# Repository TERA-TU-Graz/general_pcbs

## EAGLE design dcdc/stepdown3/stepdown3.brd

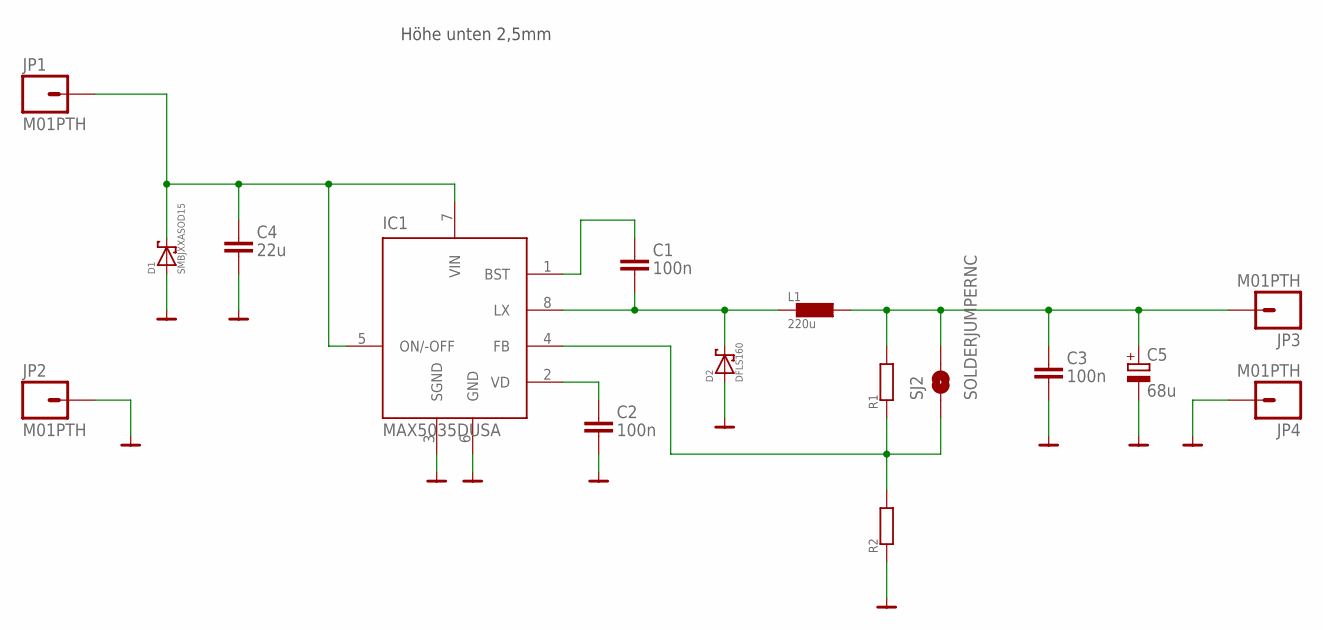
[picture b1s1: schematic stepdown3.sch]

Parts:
C1, C2, C3: 100n; C0805
C4: 22u; CKG57N
C5: 68u; CT6032
D1: SMBJXXASOD15; SOD15
D2: DFLS160; POWERDI123
IC1: MAX5035DUSA; SO08
JP1, JP2, JP3, JP4: M01PTH; 1X01
L1: 220u; L_RM5MM
R1, R2: R; R0805
SJ2: SOLDERJUMPERNC; SJ_2S

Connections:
GND: C2.1, C3.1, C4.P$1 (1), C5.-, D1.A, D2.A, IC1.3 (SGND), IC1.6 (GND), JP2.1, JP4.1, R2.1
LX: C1.1, D2.K (D), IC1.8 (LX), L1.P$1 (1)
unnamed: IC1.4 (FB), R1.1, R2.2, SJ2.1
unnamed: C1.2, IC1.1 (BST)
unnamed: C2.2, IC1.2 (VD)
VIN: C4.P$2 (2), D1.K, IC1.5 (ON/-OFF), IC1.7 (VIN), JP1.1
VOUT: C3.2, C5.+, JP3.1, L1.P$2 (2), R1.2, SJ2.2

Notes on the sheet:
Höhe unten 2,5mm

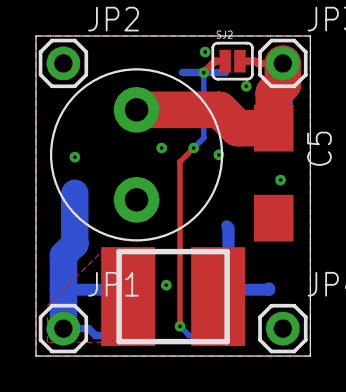
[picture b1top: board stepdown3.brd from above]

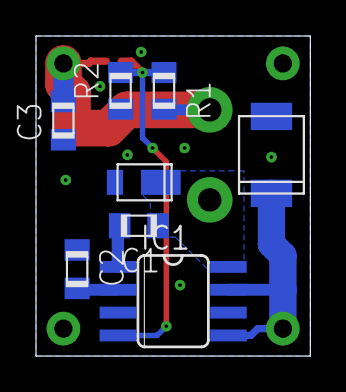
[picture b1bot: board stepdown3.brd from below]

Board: 4 copper layers, 15.2 x 17.8 mm, 16 parts (8 on the bottom side), 7 nets.

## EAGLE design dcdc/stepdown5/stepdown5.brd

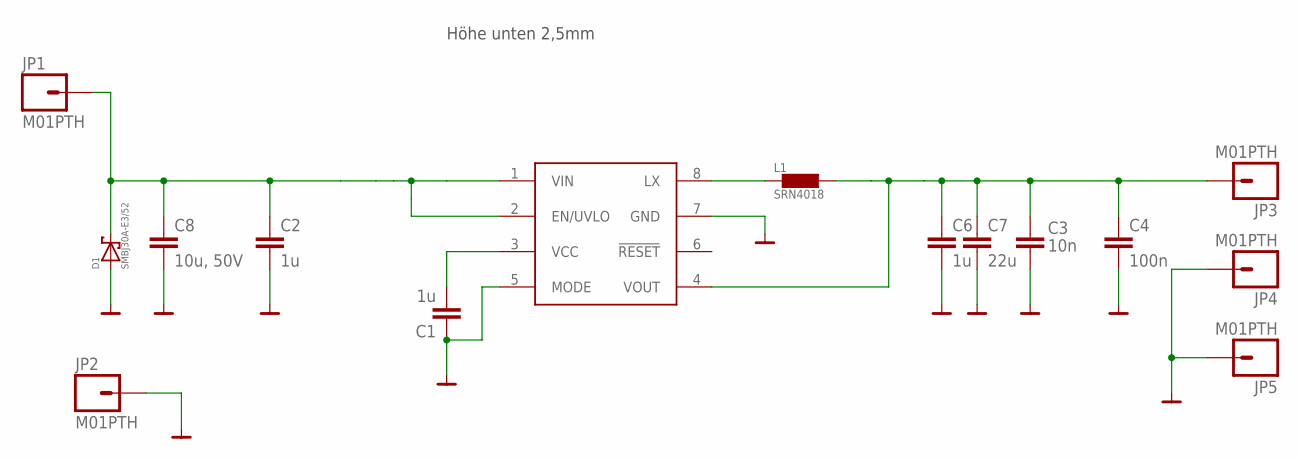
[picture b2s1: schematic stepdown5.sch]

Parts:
C1: 1u; C0603
C2: 1u; C1206
C3: 10n; C0805
C4: 100n; C0805
C6: 1u; C0805
C7: 22u; C1206
C8: 10u, 50V; C1210
D1: SMBJ30A-E3/52; SOD15
IC1: MAX15062; 8TDFN
JP1, JP2, JP3, JP4, JP5: M01PTH; 1X01
L1: SRN4018

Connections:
GND: C1.1, C2.2, C3.1, C4.2, C6.2, C7.2, C8.2, D1.A, IC1.5 (MODE), IC1.7 (GND), JP2.1, JP4.1, JP5.1
unnamed: IC1.8 (LX), L1.P$1 (1)
unnamed: C1.2, IC1.3 (VCC)
VIN: C2.1, C8.1, D1.K, IC1.1 (VIN), IC1.2 (EN/UVLO), JP1.1
VOUT: C3.2, C4.1, C6.1, C7.1, IC1.4 (VOUT), JP3.1, L1.P$2 (2)

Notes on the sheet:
Höhe unten 2,5mm

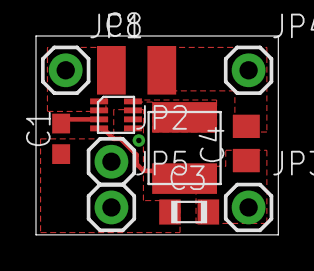
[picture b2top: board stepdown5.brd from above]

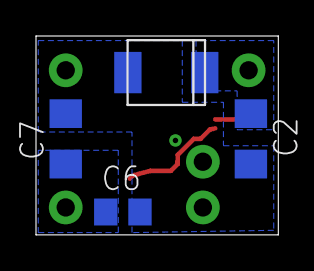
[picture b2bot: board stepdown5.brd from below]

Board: 4 copper layers, 13.5 x 11.0 mm, 15 parts (4 on the bottom side), 5 nets.

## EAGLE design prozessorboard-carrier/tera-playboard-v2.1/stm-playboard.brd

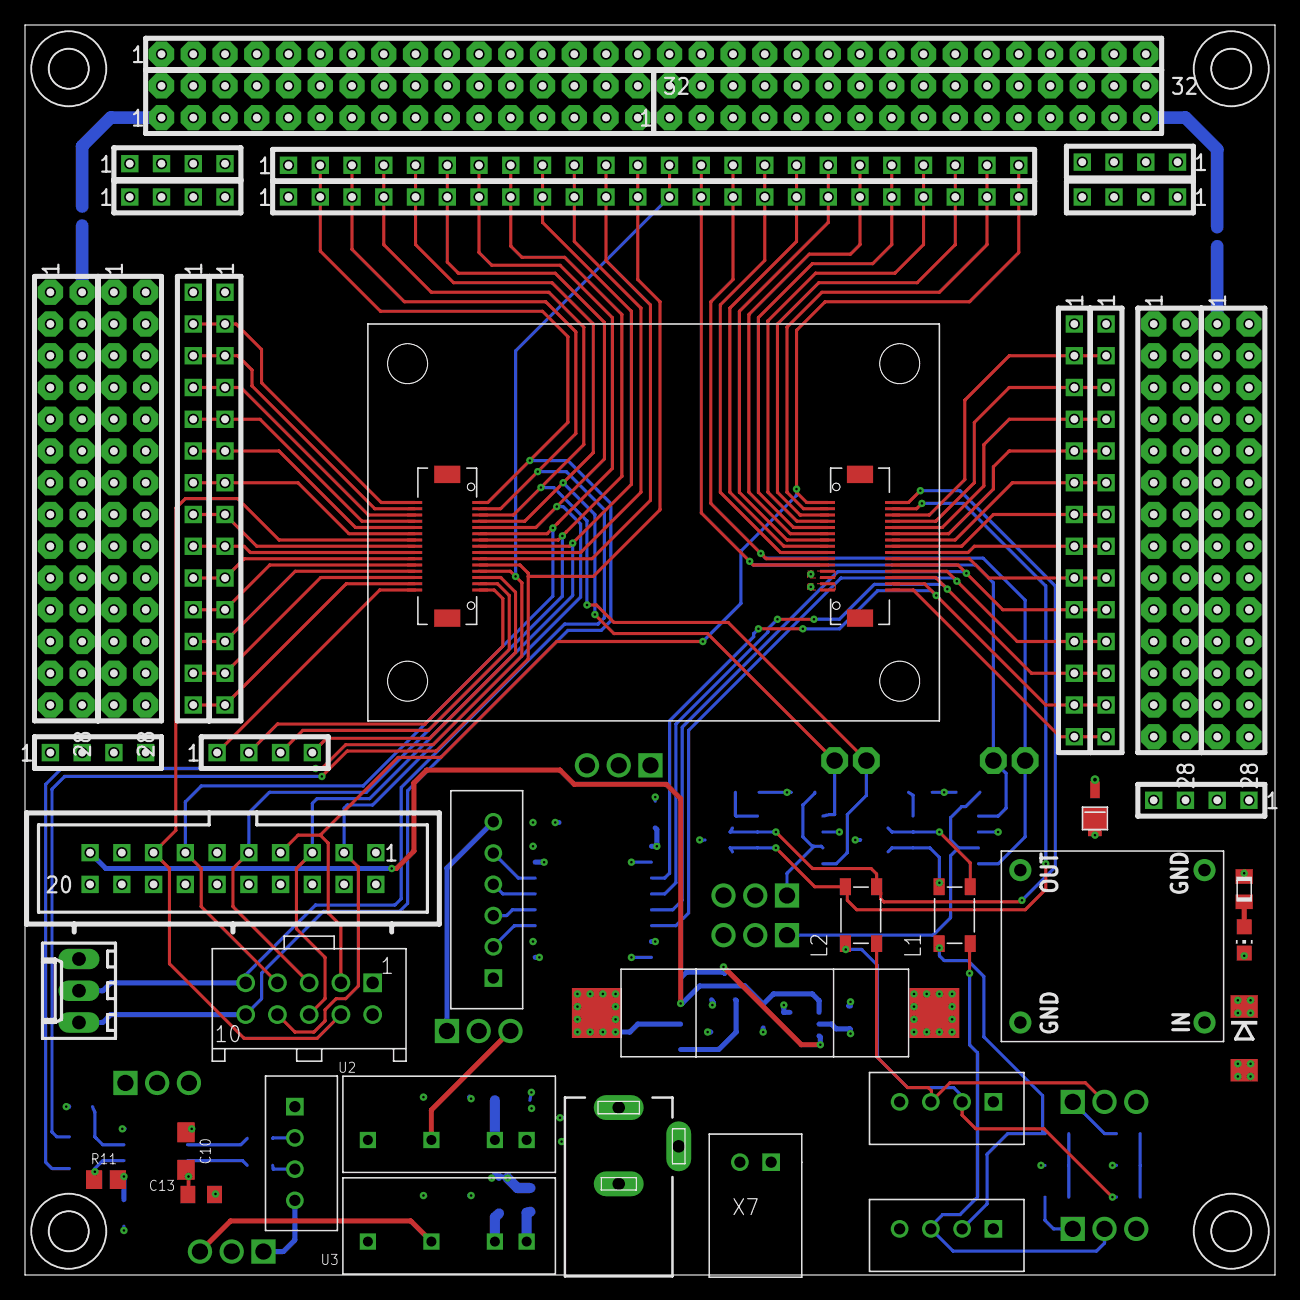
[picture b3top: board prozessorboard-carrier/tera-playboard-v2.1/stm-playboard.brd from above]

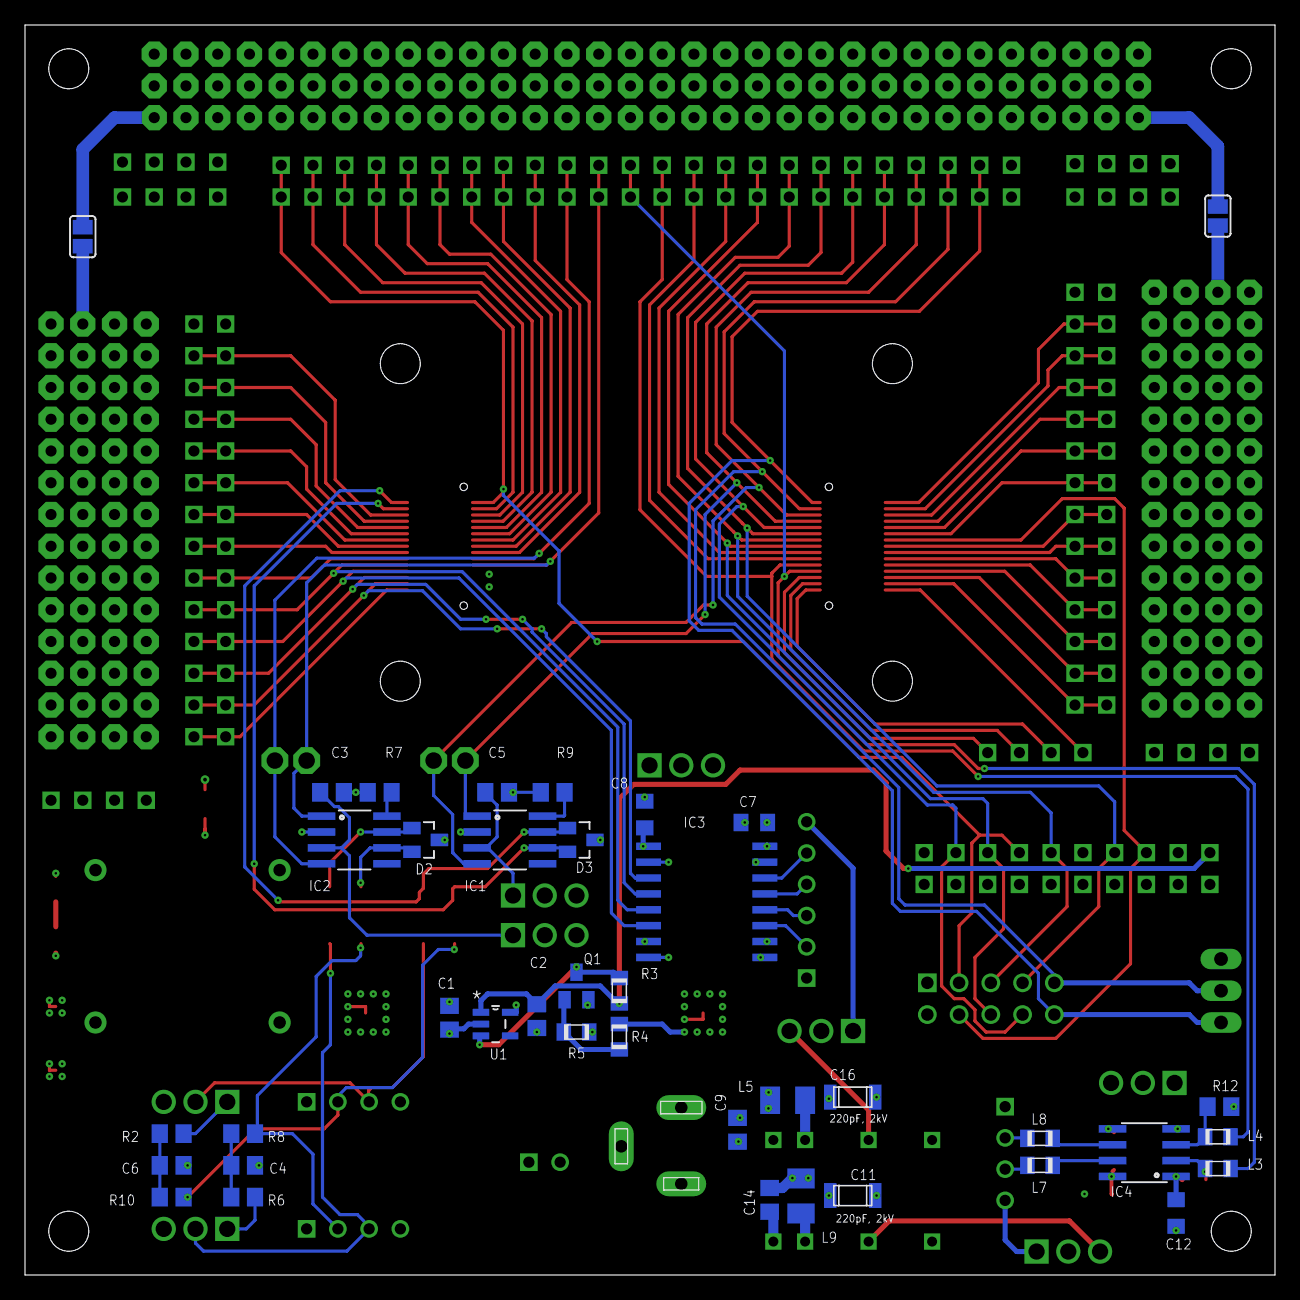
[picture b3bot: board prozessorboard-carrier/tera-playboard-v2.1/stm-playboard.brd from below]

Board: 4 copper layers, 100.0 x 100.0 mm, 98 parts (39 on the bottom side), 104 nets.

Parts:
C1, C2: 1u; C0805
C3, C5, C7, C8, C12, C13: 100n; C0805
C4, C6: 47n; C0805
C9, C14: 4,7uF, 50V; C0805
C10: 10u; SMC_A
C11, C16: 220pF, 2kV; C1210_HV
D1: 18V; DO214AA
D2, D3: NUP2105LT1G|SOT23; SOT23
H1, H2, H3, H4: MOUNT-HOLE3.2; 3,2
IC1, IC2: SN65HVD230D; SO08
IC3: ISO7241; R-PDSO-G16
IC4: ADUM1250; SO08
J1: DCJ0303
JTAG: X20R-IDC
L1, L2: ACT45B-510-2P-TL003; ACT45B
L3, L4, L7, L8: R0805
L5, L9: 4,7uH, 1,2A; L3225M
LED1: green; CHIP-LED0805
PROZ1: STM32F4_PROZESSORBOARDRPZ; STM32F4_PROZESSORBOARD
Q1: BSH105; SOT23
R1: 240R; R0805
R2, R6, R8, R10: 60R; R0805
R3, R4: 10k; R0805
R5: 15k; R0805
R7, R9: 50k; R0805
R11, R12: 15K; R0805
SERIAL: RS232V; 6410-03
SJ1, SJ2: SJ
S_CAN1, S_CAN1_ROFF, S_CAN2, S_CAN2_ROFF: JUMPER_OR; J_OR
S_I2C, S_I2C1: JUMPER_OR; J_OR
S_SPI, S_SPI1: JUMPER_OR; J_OR
TERA-DC/DC1: MAX5035_STEPDOWN3
TERA-DEBUG: TERA-PROG-DEBUG-10GERADE; 90130-1110
TP1, TP2, TP3, TP4: TPPAD1-13; P1-13
U1: ADP122AUJZ-3.3-R7; SOT95P280X100-5N
U2, U3: TMR 1-1211; TMR_1-??1?
U$2: FUSE20X5SMD; FUSE20X5-SMD
U$3: SM2T3V3A
X1, X23: X24R-SIL
X2, X14, X16, X20: X14R-SIL
X3, X4, X5, X6, X17, X18, X19: X04R-SIL
X7: S2B-XH
X8, X22: X32N-DIL
X9, X21, X24: B4B-XH
X10, X11, X12, X13: X28N-DIL
X15: X32N-SIL
X26: B6B-XH

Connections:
+3V3: C1.1, JTAG.1, PROZ1.45, PROZ1.46, R1.2, S_CAN1.P$1, S_CAN2.P$1, S_I2C.P$1, S_SPI.P$1, TERA-DC/DC1.VOUT, TERA-DEBUG.2, U1.5, U$3.P$2, X3.3, X3.4, X4.3, X4.4, X5.3, X5.4, X6.3, X6.4, X17.3, X17.4, X18.3, X18.4
+5V: C2.1, JTAG.19, R3.2, U1.1
CAN1_H: L2.P$1, S_CAN1_ROFF.P$1, X9.P$3
CAN1_L: L2.P$3, R10.2, X9.P$2
CAN2_H: L1.P$1, S_CAN2_ROFF.P$1, X21.P$3
CAN2_H0: D2.1, IC2.7, L1.P$2
CAN2_L: L1.P$3, R8.2, X21.P$2
CAN2_L0: D2.2, IC2.6, L1.P$4
CANP_H: D3.1, IC1.7, L2.P$2, PROZ1.31
CANP_L: D3.2, IC1.6, L2.P$4, PROZ1.32
GND: C1.2, C2.2, C3.2, C4.2, C5.2, C6.2, C8.1, C9.2, C11.P$1, C12.1, C14.2, C16.P$1, D1.A, D2.3, D3.3, IC1.2, IC2.2, IC3.2, IC3.8, IC4.4, J1.3, JTAG.4, JTAG.6, JTAG.8, JTAG.10, JTAG.12, JTAG.14, JTAG.16, JTAG.18, JTAG.20, LED1.C, PROZ1.47, PROZ1.48, Q1.2, R5.1, R7.1, R9.1, SERIAL.1, TERA-DC/DC1.GND@1, TERA-DC/DC1.GND@2, TERA-DEBUG.1, U1.2, U2.P$1, U3.P$1, U$3.P$1, U$3.P$11, X1.1, X2.1, X3.1, X3.2, X4.1, X4.2, X5.1, X5.2, X6.1, X6.2, X7.P$1, X9.P$1, X14.1, X16.1, X17.1, X17.2, X18.1, X18.2, X20.1, X21.P$1, X23.1
GND_SLAVE: C10.-, C11.P$2, C13.1, IC4.5, U3.P$6, X24.P$1
I2C1-SCL: IC4.3, L4.2, R12.1
I2C1-SCL1: L8.1, X24.P$2
I2C1-SDA: IC4.2, L3.2, R11.1
I2C1-SDA1: L7.1, X24.P$3
LDO_EN: Q1.3, R3.1, U1.3
unnamed: LED1.A, R1.1
unnamed: C6.1, R2.1, R10.1
unnamed: PROZ1.6, X19.4
unnamed: SJ2.1, X8.31
unnamed: SJ1.2, X12.2
unnamed: PROZ1.1, X19.1
unnamed: PROZ1.4, X19.3
unnamed: PROZ1.2, X19.2
unnamed: SJ2.2, X13.1
unnamed: SJ1.1, X22.1
unnamed: Q1.1, R4.1, R5.2
unnamed: IC4.7, L7.2
unnamed: IC4.6, L8.2
unnamed: C5.1, IC1.3, S_CAN1.P$2
unnamed: C3.1, IC2.3, S_CAN2.P$2
unnamed: IC1.8, R9.2
unnamed: C4.1, R6.1, R8.1
unnamed: R2.2, S_CAN1_ROFF.P$2
unnamed: IC2.8, R7.2
unnamed: R6.2, S_CAN2_ROFF.P$2
unnamed: C12.2, IC4.1, R11.2, R12.2, S_I2C.P$2
unnamed: C8.2, IC3.1, IC3.7, S_SPI.P$2
unnamed: L5.1, U2.P$2
unnamed: S_I2C1.P$2, X24.P$4
unnamed: S_I2C1.P$3, U3.P$4
unnamed: S_SPI1.P$2, X26.P$6
unnamed: S_SPI1.P$3, U2.P$4
unnamed: L9.1, U3.P$2
NRST: JTAG.15, PROZ1.17, TERA-DEBUG.4
PA0: PROZ1.7, X2.12, X16.12
PA1: PROZ1.5, X2.13, X16.13
PA2: PROZ1.3, X2.14, X16.14
PA3: PROZ1.44, X14.14, X20.14
PA4: IC3.3, PROZ1.43, X14.13, X20.13
PA5: IC3.4, PROZ1.60, X14.12, X20.12
PA6: IC3.6, PROZ1.42, X14.11, X20.11
PA7: IC3.5, PROZ1.41, X14.10, X20.10
PA8: PROZ1.56, X1.21, X23.21
PA9: PROZ1.57, X1.22, X23.22
PA10: PROZ1.58, X1.23, X23.23
PA11: IC1.4, PROZ1.26, TP2.TP, X1.4, X23.4
PA12: IC1.1, PROZ1.24, TP1.TP, X1.5, X23.5
PA13: JTAG.7, PROZ1.59, TERA-DEBUG.3, X1.24, X23.24
PA14: JTAG.9, PROZ1.18, TERA-DEBUG.5, X1.8, X23.8
PA15: JTAG.5, PROZ1.16, TERA-DEBUG.6, X1.9, X23.9
PB0: PROZ1.38, X14.7, X20.7
PB1: PROZ1.37, X14.6, X20.6
PB2: PROZ1.36, X14.5, X20.5
PB3: JTAG.13, PROZ1.20, TERA-DEBUG.7, X1.7, X23.7
PB4: JTAG.3, PROZ1.22, TERA-DEBUG.8, X1.6, X23.6
PB5: PROZ1.25, X2.4, X16.4
PB6: PROZ1.14, X1.10, X23.10
PB7: PROZ1.12, X1.11, X23.11
PB8: L4.1, PROZ1.10, X1.12, X23.12
PB9: L3.1, PROZ1.8, X1.13, X23.13
PB10: PROZ1.35, X14.4, X20.4
PB11: PROZ1.34, X14.3, X20.3
PB12: IC2.4, PROZ1.50, TP4.TP, X1.15, X23.15
PB13: IC2.1, PROZ1.49, TP3.TP, X1.14, X23.14
PB14: PROZ1.33, X14.2, X20.2
PB15: PROZ1.51, X1.16, X23.16
PC0: PROZ1.15, X2.8, X16.8
PC1: PROZ1.13, X2.9, X16.9
PC2: PROZ1.11, X2.10, X16.10
PC3: PROZ1.9, X2.11, X16.11
PC4: PROZ1.40, X14.9, X20.9
PC5: PROZ1.39, X14.8, X20.8
PC6: PROZ1.52, X1.17, X23.17
PC7: PROZ1.53, X1.18, X23.18
PC8: PROZ1.54, X1.19, X23.19
PC9: PROZ1.55, X1.20, X23.20
PC10: PROZ1.28, SERIAL.2, TERA-DEBUG.9, X1.3, X23.3
PC11: PROZ1.30, SERIAL.3, TERA-DEBUG.10, X1.2, X23.2
PC12: PROZ1.29, X2.2, X16.2
PC13: PROZ1.23, X2.5, X16.5
PC14: PROZ1.21, X2.6, X16.6
PC15: PROZ1.19, X2.7, X16.7
PD2: PROZ1.27, X2.3, X16.3
SPI_MISO: IC3.11, X26.P$2
SPI_MOSI: IC3.12, X26.P$3
SPI_NCS: IC3.14, X26.P$5
SPI_SCK: IC3.13, X26.P$4
SPI_V+: C7.2, IC3.10, IC3.16, S_SPI1.P$1
SPI_V-: C7.1, C16.P$2, IC3.9, IC3.15, U2.P$6, X26.P$1
VBAT: J1.1, R4.2, U$2.P$3, X7.P$2
VBAT_FUSED: C9.1, C14.1, D1.C, L5.2, L9.2, TERA-DC/DC1.VIN, U$2.P$4, X9.P$4, X21.P$4
VDD-ISO1: C10.+, C13.2, IC4.8, S_I2C1.P$1

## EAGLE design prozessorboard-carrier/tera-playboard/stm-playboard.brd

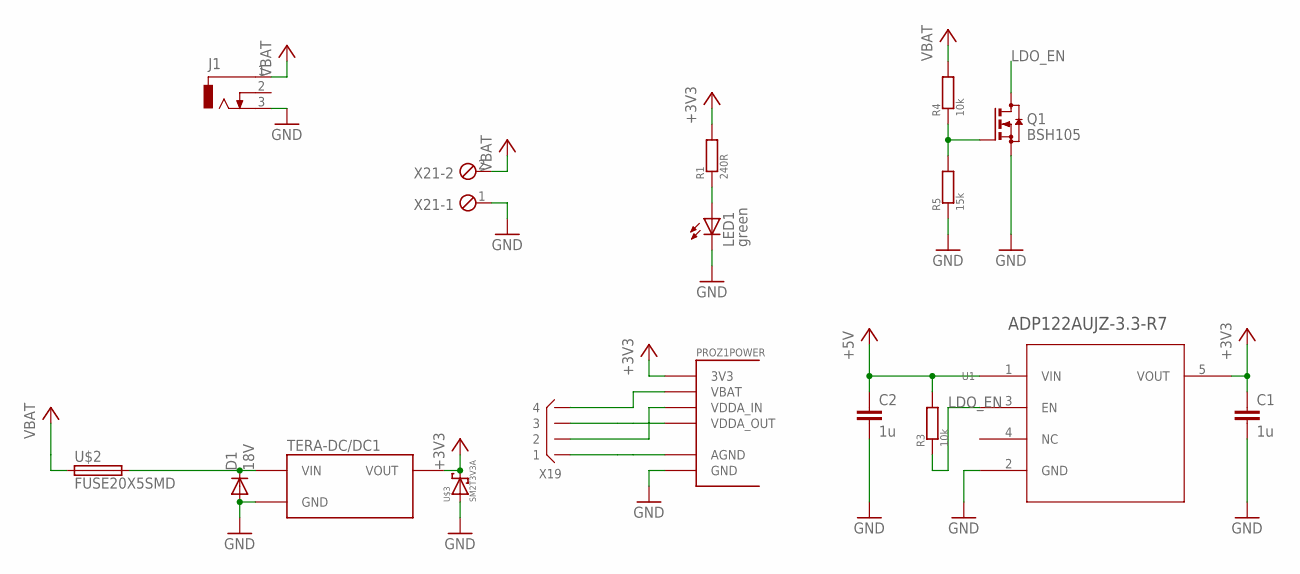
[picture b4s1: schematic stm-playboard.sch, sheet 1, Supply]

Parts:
C1, C2: 1u; C0805
D1: 18V; DO214AA
J1: DCJ0303
LED1: green; CHIP-LED0805
PROZ1: STM32F4_PROZESSORBOARDRPZ; STM32F4_PROZESSORBOARD
Q1: BSH105; SOT23
R1: 240R; R0805
R3, R4: 10k; R0805
R5: 15k; R0805
TERA-DC/DC1: MAX5035_STEPDOWN3
U1: ADP122AUJZ-3.3-R7; SOT95P280X100-5N
U$2: FUSE20X5SMD; FUSE20X5-SMD
U$3: SM2T3V3A
X19: X04N; X04N-SIL
X21: MPT2; 2POL254

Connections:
+3V3: C1.1, PROZ1.45 (3V3), PROZ1.46 (3V3), R1.2, TERA-DC/DC1.VOUT, U1.5 (VOUT), U$3.P$2; also elsewhere on the board
+5V: C2.1, R3.2, U1.1 (VIN); also elsewhere on the board
GND: C1.2, C2.2, D1.A, J1.3, LED1.C, PROZ1.47 (GND), PROZ1.48 (GND), Q1.2 (S), R5.1, TERA-DC/DC1.GND@1 (GND), TERA-DC/DC1.GND@2 (GND), U1.2 (GND), U$3.P$1, U$3.P$11, X21.1; also elsewhere on the board
LDO_EN: Q1.3 (D), R3.1, U1.3 (EN)
unnamed: D1.C, TERA-DC/DC1.VIN, U$2.P$4 (2)
unnamed: LED1.A, R1.1
unnamed: PROZ1.6 (VBAT), X19.4
unnamed: PROZ1.1 (AGND), X19.1
unnamed: PROZ1.4 (VDDA_OUT), X19.3
unnamed: PROZ1.2 (VDDA_IN), X19.2
unnamed: Q1.1 (G), R4.1, R5.2
VBAT: J1.1, R4.2, U$2.P$3 (1), X21.2; also elsewhere on the board

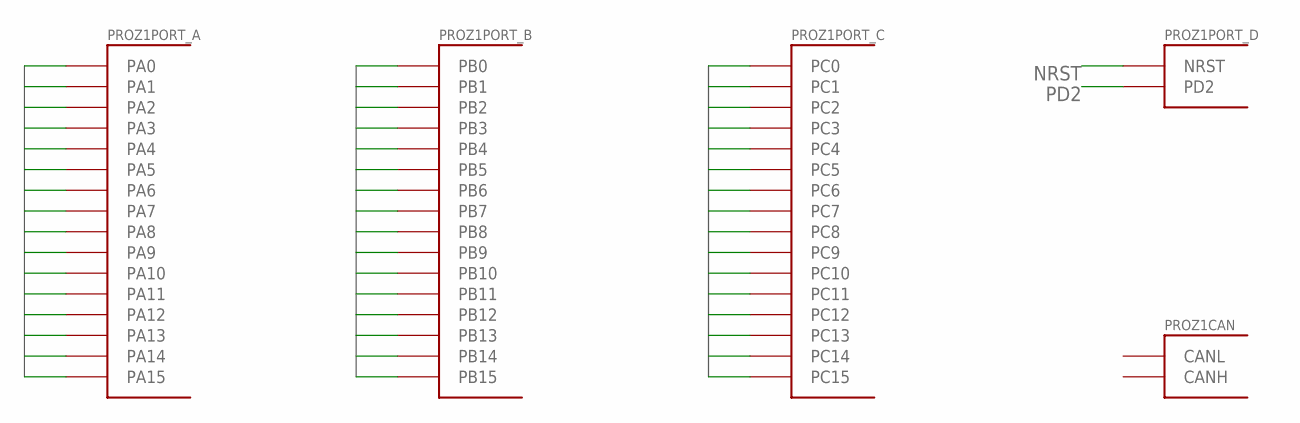
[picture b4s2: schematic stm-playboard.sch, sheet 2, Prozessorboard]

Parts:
PROZ1: STM32F4_PROZESSORBOARDRPZ; STM32F4_PROZESSORBOARD

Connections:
NRST: PROZ1.17 (NRST); also elsewhere on the board
PA0: PROZ1.7 (PA0); also elsewhere on the board
PA1: PROZ1.5 (PA1); also elsewhere on the board
PA2: PROZ1.3 (PA2); also elsewhere on the board
PA3: PROZ1.44 (PA3); also elsewhere on the board
PA4: PROZ1.43 (PA4); also elsewhere on the board
PA5: PROZ1.60 (PA5); also elsewhere on the board
PA6: PROZ1.42 (PA6); also elsewhere on the board
PA7: PROZ1.41 (PA7); also elsewhere on the board
PA8: PROZ1.56 (PA8); also elsewhere on the board
PA9: PROZ1.57 (PA9); also elsewhere on the board
PA10: PROZ1.58 (PA10); also elsewhere on the board
PA11: PROZ1.26 (PA11); also elsewhere on the board
PA12: PROZ1.24 (PA12); also elsewhere on the board
PA13: PROZ1.59 (PA13); also elsewhere on the board
PA14: PROZ1.18 (PA14); also elsewhere on the board
PA15: PROZ1.16 (PA15); also elsewhere on the board
PB0: PROZ1.38 (PB0); also elsewhere on the board
PB1: PROZ1.37 (PB1); also elsewhere on the board
PB2: PROZ1.36 (PB2); also elsewhere on the board
PB3: PROZ1.20 (PB3); also elsewhere on the board
PB4: PROZ1.22 (PB4); also elsewhere on the board
PB5: PROZ1.25 (PB5); also elsewhere on the board
PB6: PROZ1.14 (PB6); also elsewhere on the board
PB7: PROZ1.12 (PB7); also elsewhere on the board
PB8: PROZ1.10 (PB8); also elsewhere on the board
PB9: PROZ1.8 (PB9); also elsewhere on the board
PB10: PROZ1.35 (PB10); also elsewhere on the board
PB11: PROZ1.34 (PB11); also elsewhere on the board
PB12: PROZ1.50 (PB12); also elsewhere on the board
PB13: PROZ1.49 (PB13); also elsewhere on the board
PB14: PROZ1.33 (PB14); also elsewhere on the board
PB15: PROZ1.51 (PB15); also elsewhere on the board
PC0: PROZ1.15 (PC0); also elsewhere on the board
PC1: PROZ1.13 (PC1); also elsewhere on the board
PC2: PROZ1.11 (PC2); also elsewhere on the board
PC3: PROZ1.9 (PC3); also elsewhere on the board
PC4: PROZ1.40 (PC4); also elsewhere on the board
PC5: PROZ1.39 (PC5); also elsewhere on the board
PC6: PROZ1.52 (PC6); also elsewhere on the board
PC7: PROZ1.53 (PC7); also elsewhere on the board
PC8: PROZ1.54 (PC8); also elsewhere on the board
PC9: PROZ1.55 (PC9); also elsewhere on the board
PC10: PROZ1.28 (PC10); also elsewhere on the board
PC11: PROZ1.30 (PC11); also elsewhere on the board
PC12: PROZ1.29 (PC12); also elsewhere on the board
PC13: PROZ1.23 (PC13); also elsewhere on the board
PC14: PROZ1.21 (PC14); also elsewhere on the board
PC15: PROZ1.19 (PC15); also elsewhere on the board
PD2: PROZ1.27 (PD2); also elsewhere on the board

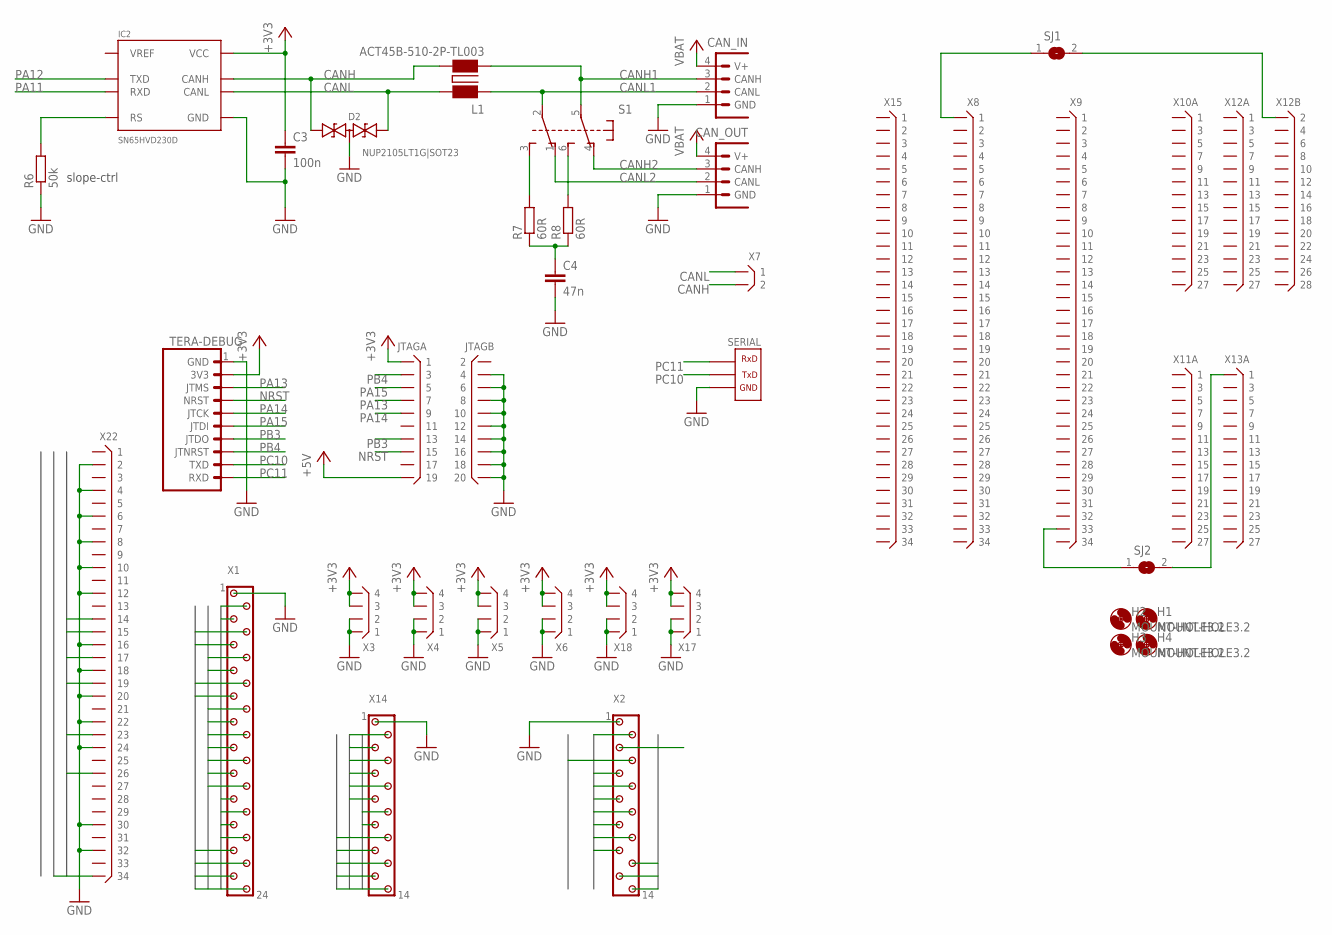
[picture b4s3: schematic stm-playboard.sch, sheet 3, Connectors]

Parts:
C3: 100n; C0805
C4: 47n; C0805
CAN_IN: CIOC_4-1-FV-A_CAN-BELEGUNG; CIOC_4-1-FV
CAN_OUT: CIOC_4-1-FV-A_CAN-BELEGUNG; CIOC_4-1-FV
D2: NUP2105LT1G|SOT23; SOT23
H1, H2, H3, H4: MOUNT-HOLE3.2; 3,2
IC2: SN65HVD230D; SO08
JTAG: X10X2; X20N-IDC
L1: ACT45B-510-2P-TL003; ACT45B
R6: 50k; R0805
R7, R8: 60R; R0805
S1: SCHIEBESCHALTER-2-WECHSLER; DPDT-M2
SERIAL: RS232H; 7395-03
SJ1, SJ2: SJ
TERA-DEBUG: TERA-PROG-DEBUG-10RECHTWINKELIG; 90130-3210
X1: XA24N; X24N-SIL
X2, X14: XA14N; X14N-SIL
X3, X4, X5, X6, X17, X18: X04N; X04N-SIL
X7: X02N; X02N-SIL
X8, X9: X34D; X34N-DIL
X10, X11, X12, X13: X14X2D; X28N-DIL
X15: X34N; X34N-SIL
X22: X34; X34N-IDC

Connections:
+3V3: C3.1, IC2.3 (VCC), JTAG.1, TERA-DEBUG.2 (3V3), X3.3, X3.4, X4.3, X4.4, X5.3, X5.4, X6.3, X6.4, X17.3, X17.4, X18.3, X18.4; also elsewhere on the board
+5V: JTAG.19; also elsewhere on the board
CANH: D2.1, IC2.7 (CANH), L1.P$2 (2), X7.2
CANH1: CAN_IN.3 (CANH), L1.P$1 (1), S1.5 (P2)
CANH2: CAN_OUT.3 (CANH), S1.4 (O2)
CANL: D2.2, IC2.6 (CANL), L1.P$4 (4), X7.1
CANL1: CAN_IN.2 (CANL), L1.P$3 (3), S1.2 (P1)
CANL2: CAN_OUT.2 (CANL), S1.1 (O1)
GND: C3.2, C4.2, CAN_IN.1 (GND), CAN_OUT.1 (GND), D2.3, IC2.2 (GND), JTAG.4, JTAG.6, JTAG.8, JTAG.10, JTAG.12, JTAG.14, JTAG.16, JTAG.18, JTAG.20, R6.1, SERIAL.1 (GND), TERA-DEBUG.1 (GND), X1.1, X2.1, X3.1, X3.2, X4.1, X4.2, X5.1, X5.2, X6.1, X6.2, X14.1, X17.1, X17.2, X18.1, X18.2, X22.2, X22.4, X22.6, X22.8, X22.10, X22.12, X22.16, X22.18, X22.20, X22.22, X22.24, X22.30, X22.32; also elsewhere on the board
unnamed: SJ2.1, X9.33
unnamed: SJ1.2, X12.2
unnamed: SJ2.2, X13.1
unnamed: SJ1.1, X8.1
unnamed: C4.1, R7.1, R8.1
unnamed: IC2.8 (RS), R6.2
unnamed: R8.2, S1.6 (S2)
unnamed: R7.2, S1.3 (S1)
NRST: JTAG.15, TERA-DEBUG.4 (NRST); also elsewhere on the board
PA0: X2.12; also elsewhere on the board
PA1: X2.13; also elsewhere on the board
PA2: X2.14; also elsewhere on the board
PA3: X14.14; also elsewhere on the board
PA4: X14.13; also elsewhere on the board
PA5: X14.12; also elsewhere on the board
PA6: X14.11; also elsewhere on the board
PA7: X14.10; also elsewhere on the board
PA8: X1.21; also elsewhere on the board
PA9: X1.22; also elsewhere on the board
PA10: X1.23; also elsewhere on the board
PA11: IC2.4 (RXD), X1.4; also elsewhere on the board
PA12: IC2.1 (TXD), X1.5; also elsewhere on the board
PA13: JTAG.7, TERA-DEBUG.3 (JTMS), X1.24; also elsewhere on the board
PA14: JTAG.9, TERA-DEBUG.5 (JTCK), X1.8; also elsewhere on the board
PA15: JTAG.5, TERA-DEBUG.6 (JTDI), X1.9; also elsewhere on the board
PB0: X14.7; also elsewhere on the board
PB1: X14.6; also elsewhere on the board
PB2: X14.5; also elsewhere on the board
PB3: JTAG.13, TERA-DEBUG.7 (JTDO), X1.7; also elsewhere on the board
PB4: JTAG.3, TERA-DEBUG.8 (JTNRST), X1.6; also elsewhere on the board
PB5: X2.4; also elsewhere on the board
PB6: X1.10; also elsewhere on the board
PB7: X1.11; also elsewhere on the board
PB8: X1.12, X22.34; also elsewhere on the board
PB9: X1.13; also elsewhere on the board
PB10: X14.4; also elsewhere on the board
PB11: X14.3; also elsewhere on the board
PB12: X1.15; also elsewhere on the board
PB13: X1.14; also elsewhere on the board
PB14: X14.2; also elsewhere on the board
PB15: X1.16; also elsewhere on the board
PC0: X2.8; also elsewhere on the board
PC1: X2.9, X22.15; also elsewhere on the board
PC2: X2.10, X22.17; also elsewhere on the board
PC3: X2.11, X22.19; also elsewhere on the board
PC4: X14.9, X22.14; also elsewhere on the board
PC5: X14.8, X22.26; also elsewhere on the board
PC6: X1.17; also elsewhere on the board
PC7: X1.18; also elsewhere on the board
PC8: X1.19, X22.23; also elsewhere on the board
PC9: X1.20; also elsewhere on the board
PC10: SERIAL.2 (TXD), TERA-DEBUG.9 (TXD), X1.3; also elsewhere on the board
PC11: SERIAL.3 (RXD), TERA-DEBUG.10 (RXD), X1.2; also elsewhere on the board
PC12: X2.2; also elsewhere on the board
PC13: X2.5; also elsewhere on the board
PC14: X2.6; also elsewhere on the board
PC15: X2.7; also elsewhere on the board
PD2: X2.3; also elsewhere on the board
VBAT: CAN_IN.4 (V+), CAN_OUT.4 (V+); also elsewhere on the board

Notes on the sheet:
slope-ctrl

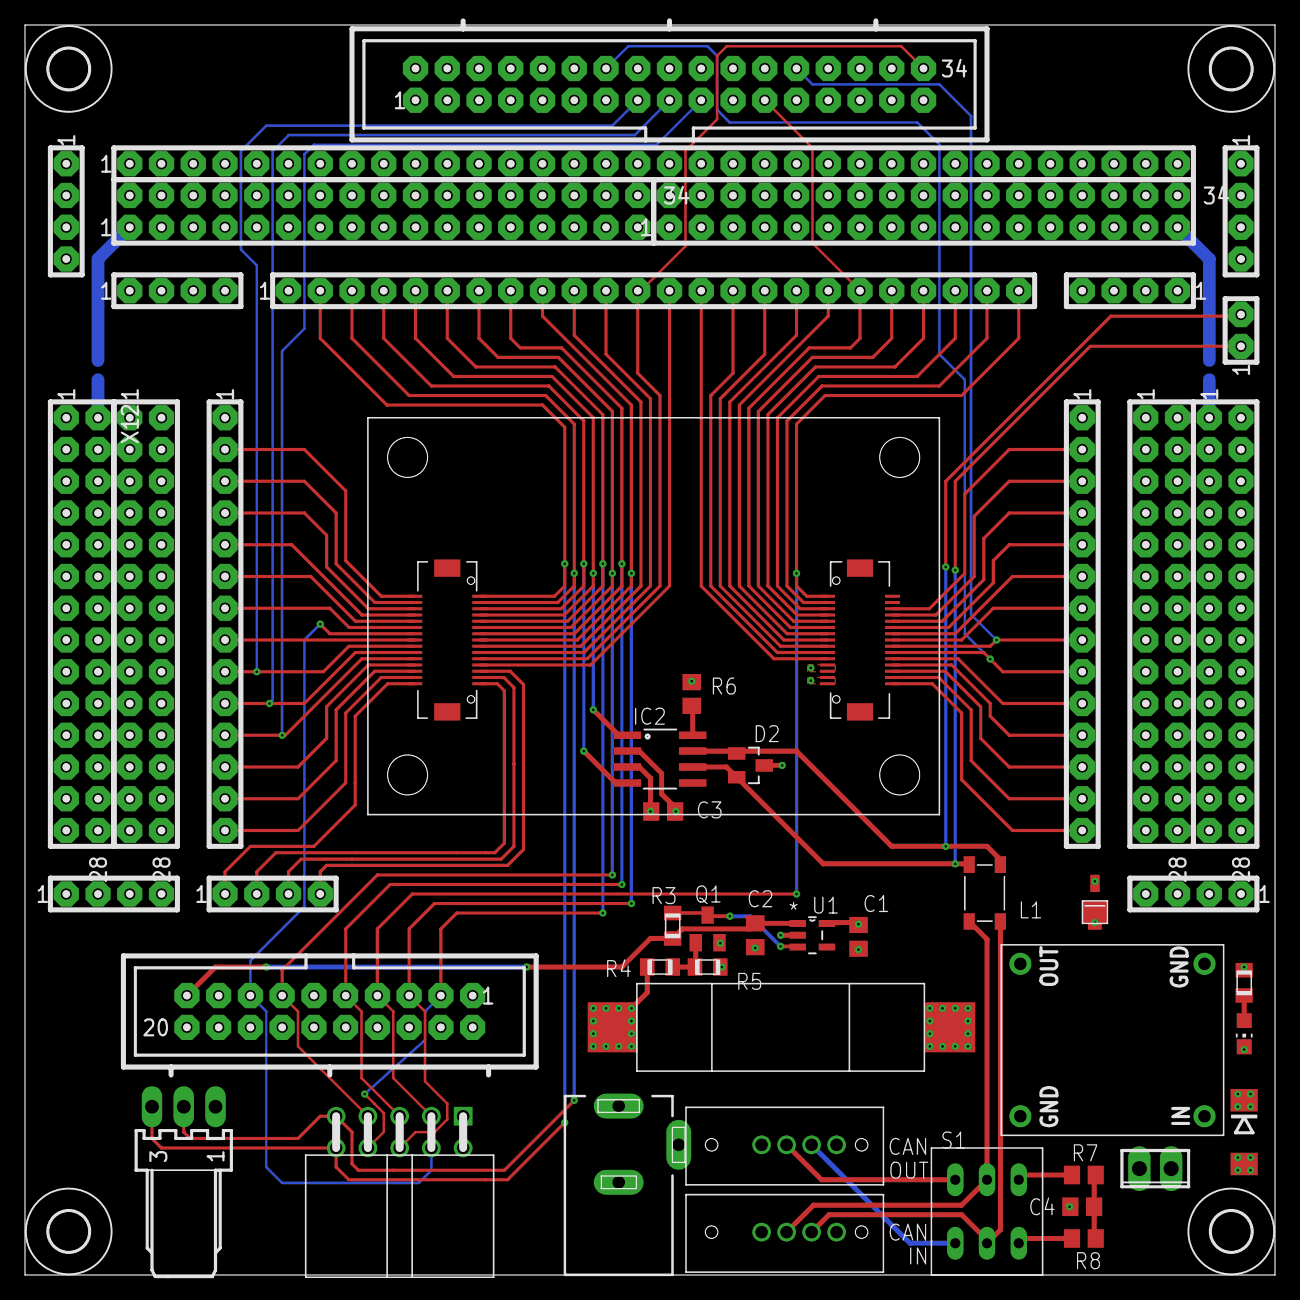
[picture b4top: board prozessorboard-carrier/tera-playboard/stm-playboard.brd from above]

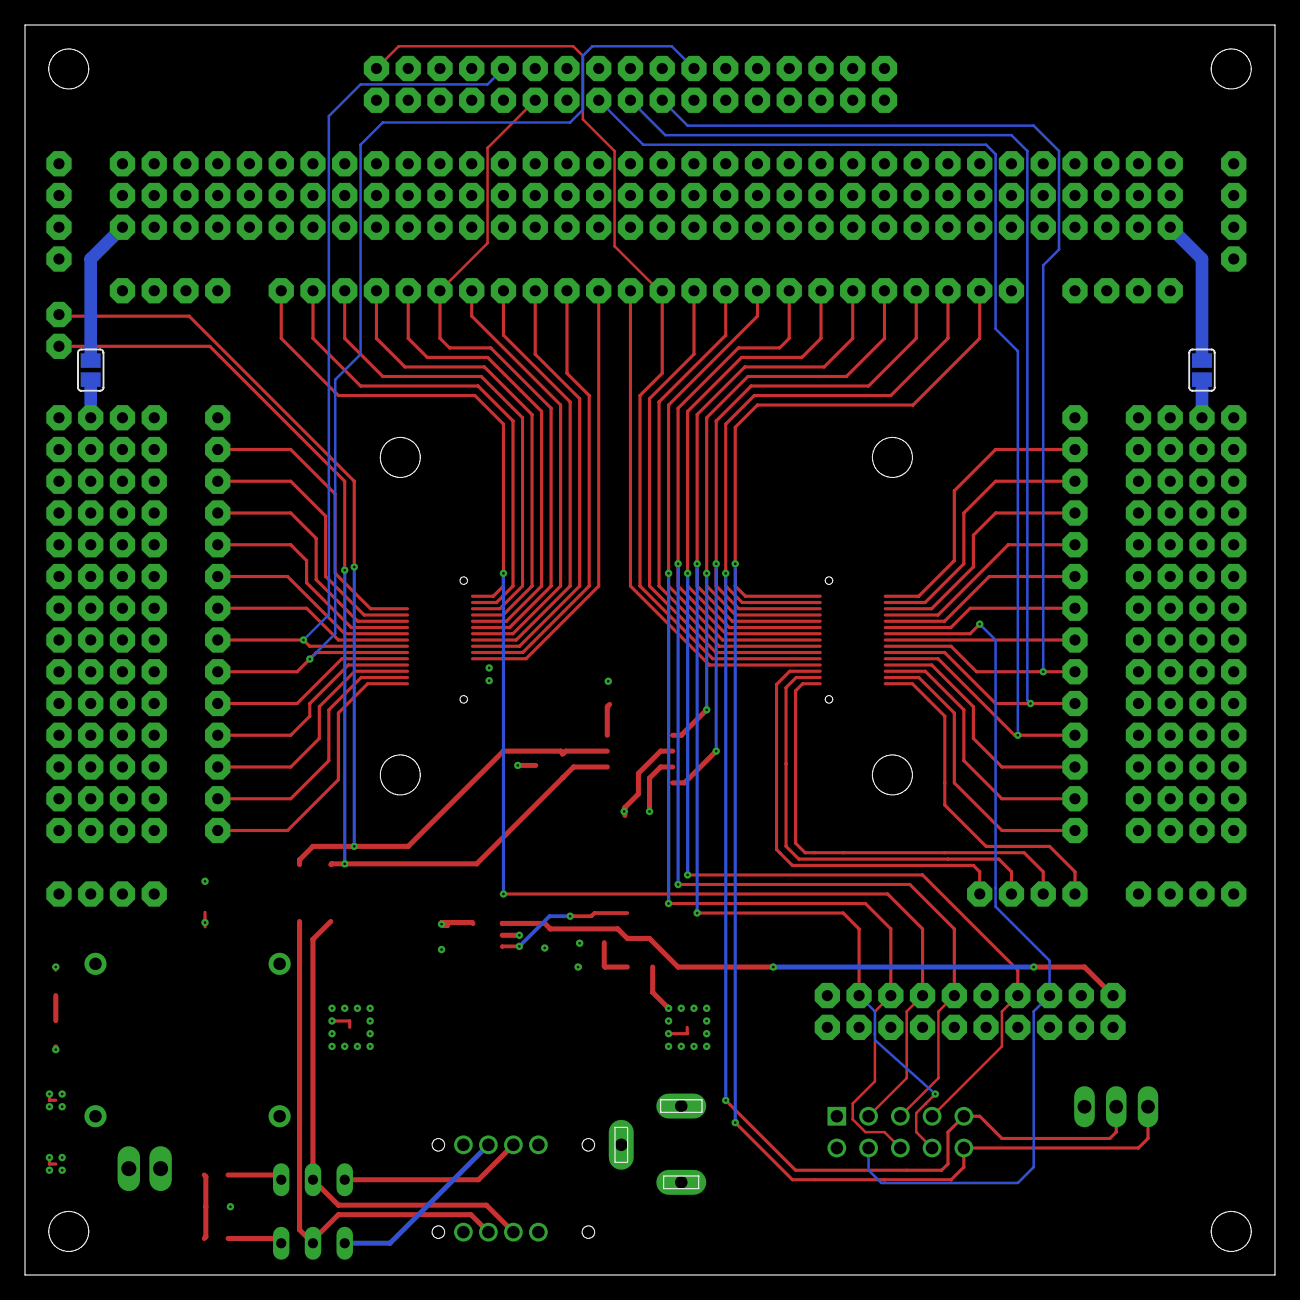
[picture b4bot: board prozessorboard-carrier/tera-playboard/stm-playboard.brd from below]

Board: 4 copper layers, 100.0 x 100.0 mm, 55 parts (2 on the bottom side), 76 nets.

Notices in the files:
parts and their libraries:
SparkFun: Licensing: CC v3.0 Share-Alike You are welcome to use this library for commercial purposes.
